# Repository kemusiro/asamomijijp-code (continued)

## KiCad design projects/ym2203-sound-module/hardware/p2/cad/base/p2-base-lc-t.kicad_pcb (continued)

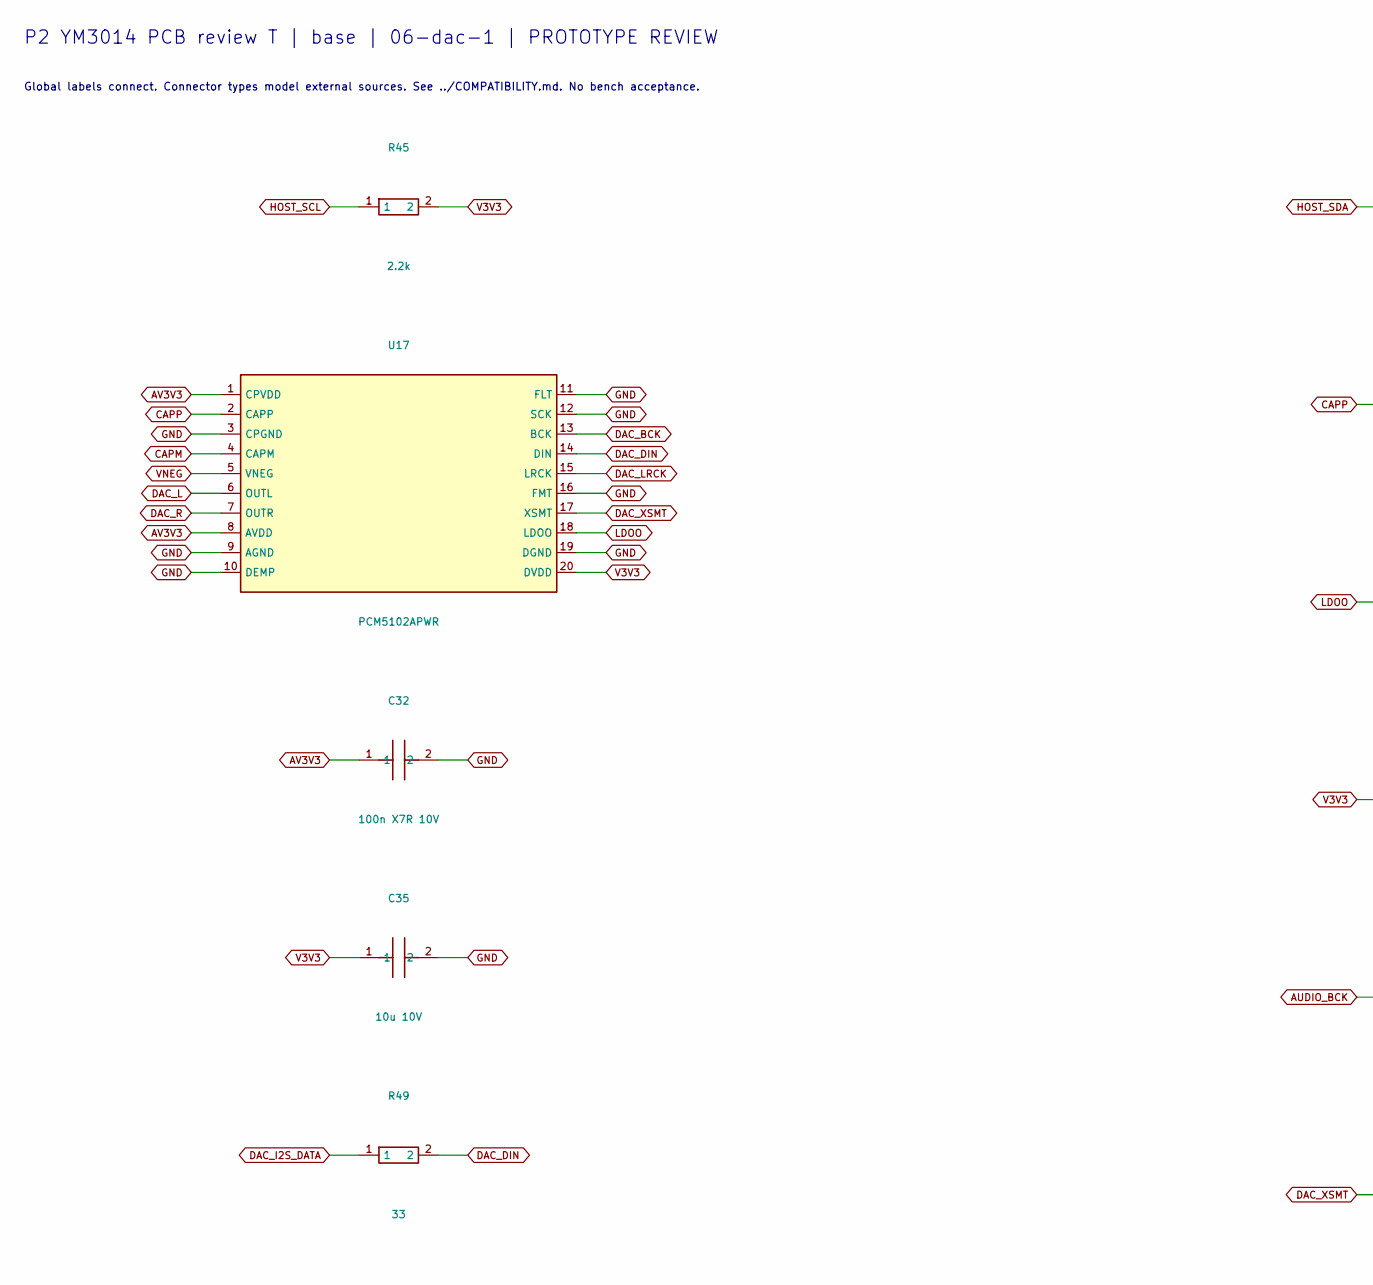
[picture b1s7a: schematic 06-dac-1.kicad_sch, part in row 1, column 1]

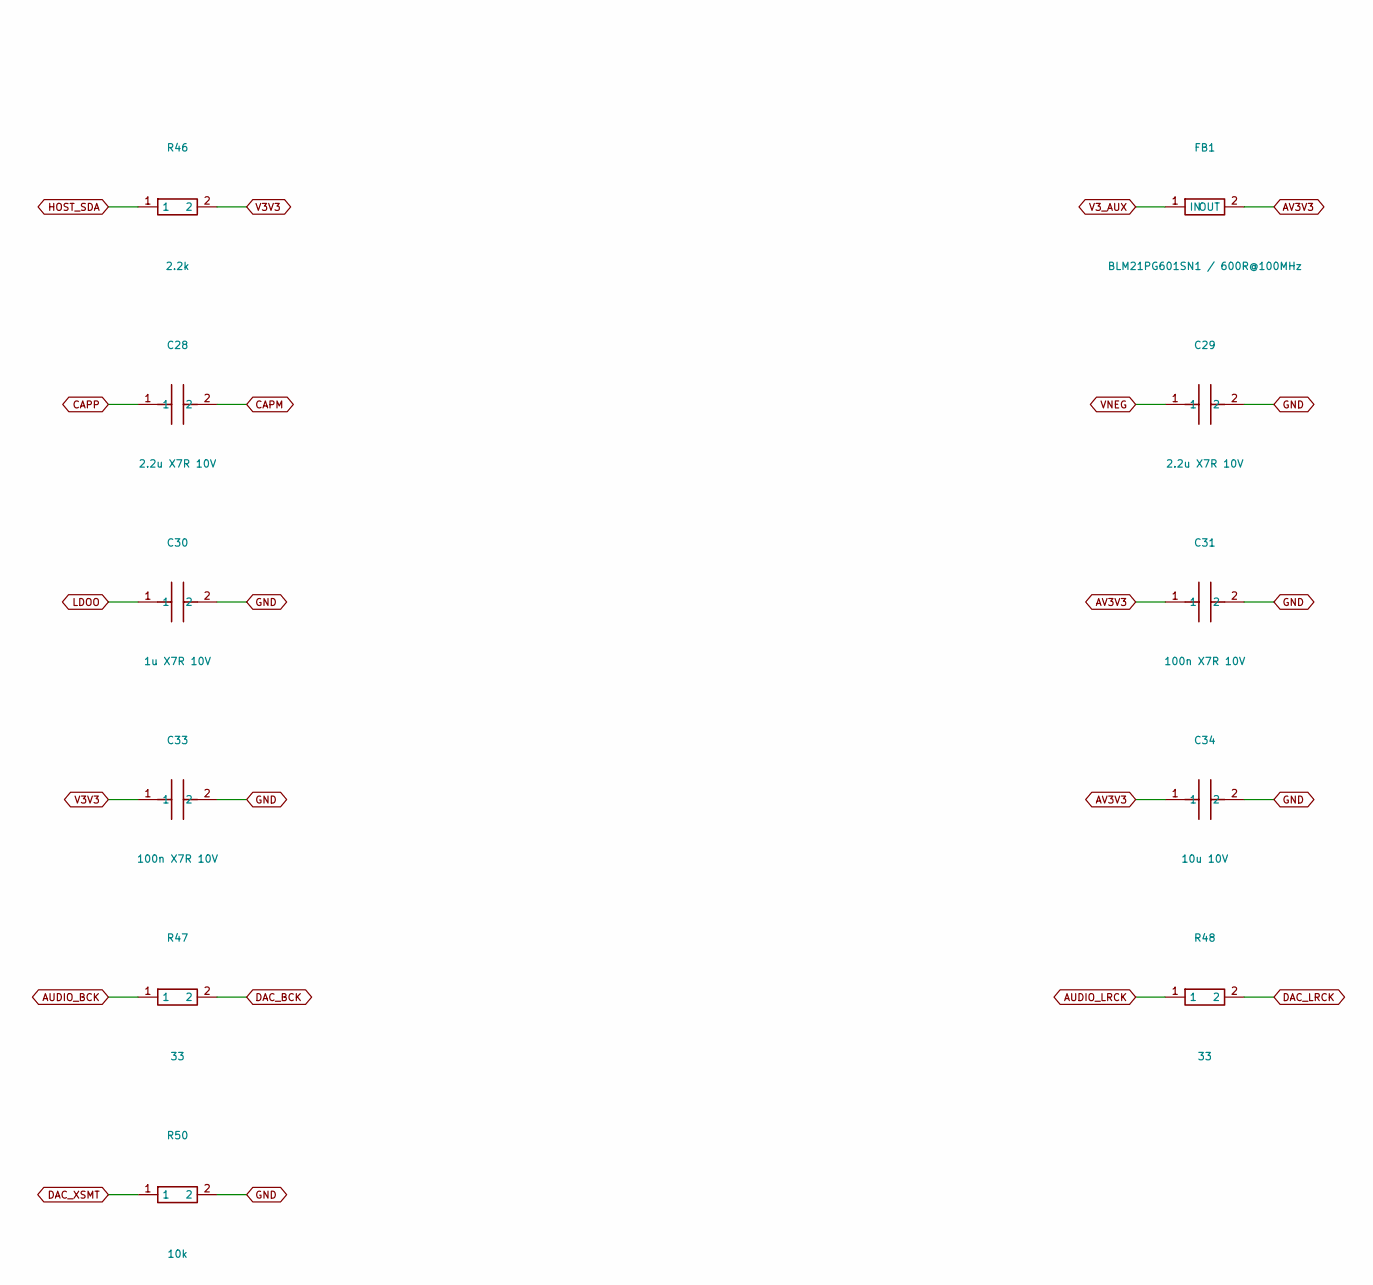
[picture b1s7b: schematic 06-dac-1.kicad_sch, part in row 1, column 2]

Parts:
C28, C29: 2.2u X7R 10V; C_0805_2012Metric
C30: 1u X7R 10V; C_0805_2012Metric
C31, C32, C33: 100n X7R 10V; C_0805_2012Metric
C34, C35: 10u 10V; C_0805_2012Metric
FB1: BLM21PG601SN1 / 600R@100MHz; L_0805_2012Metric
R45, R46: 2.2k; R_0805_2012Metric
R47, R48, R49: 33; R_0805_2012Metric
R50: 10k; R_0805_2012Metric
U17: PCM5102APWR; TSSOP-20_4.4x6.5mm_P0.65mm

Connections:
AUDIO_BCK: R47.1; also elsewhere on the board
AUDIO_LRCK: R48.1; also elsewhere on the board
AV3V3: C31.1, C32.1, C34.1, FB1.2 (OUT), U17.1 (CPVDD), U17.8 (AVDD); also elsewhere on the board
CAPM: C28.2, U17.4 (CAPM)
CAPP: C28.1, U17.2 (CAPP)
DAC_BCK: R47.2, U17.13 (BCK); also elsewhere on the board
DAC_DIN: R49.2, U17.14 (DIN); also elsewhere on the board
DAC_I2S_DATA: R49.1; also elsewhere on the board
DAC_L: U17.6 (OUTL); also elsewhere on the board
DAC_LRCK: R48.2, U17.15 (LRCK); also elsewhere on the board
DAC_R: U17.7 (OUTR); also elsewhere on the board
DAC_XSMT: R50.1, U17.17 (XSMT); also elsewhere on the board
GND: C29.2, C30.2, C31.2, C32.2, C33.2, C34.2, C35.2, R50.2, U17.3 (CPGND), U17.9 (AGND), U17.10 (DEMP), U17.11 (FLT), U17.12 (SCK), U17.16 (FMT), U17.19 (DGND); also elsewhere on the board
HOST_SCL: R45.1; also elsewhere on the board
HOST_SDA: R46.1; also elsewhere on the board
LDOO: C30.1, U17.18 (LDOO)
V3V3: C33.1, C35.1, R45.2, R46.2, U17.20 (DVDD); also elsewhere on the board
V3_AUX: FB1.1 (IN); also elsewhere on the board
VNEG: C29.1, U17.5 (VNEG)

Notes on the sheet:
P2 YM3014 PCB review T | base | 06-dac-1 | PROTOTYPE REVIEW
Global labels connect. Connector types model external sources. See ../COMPATIBILITY.md. No bench acceptance.

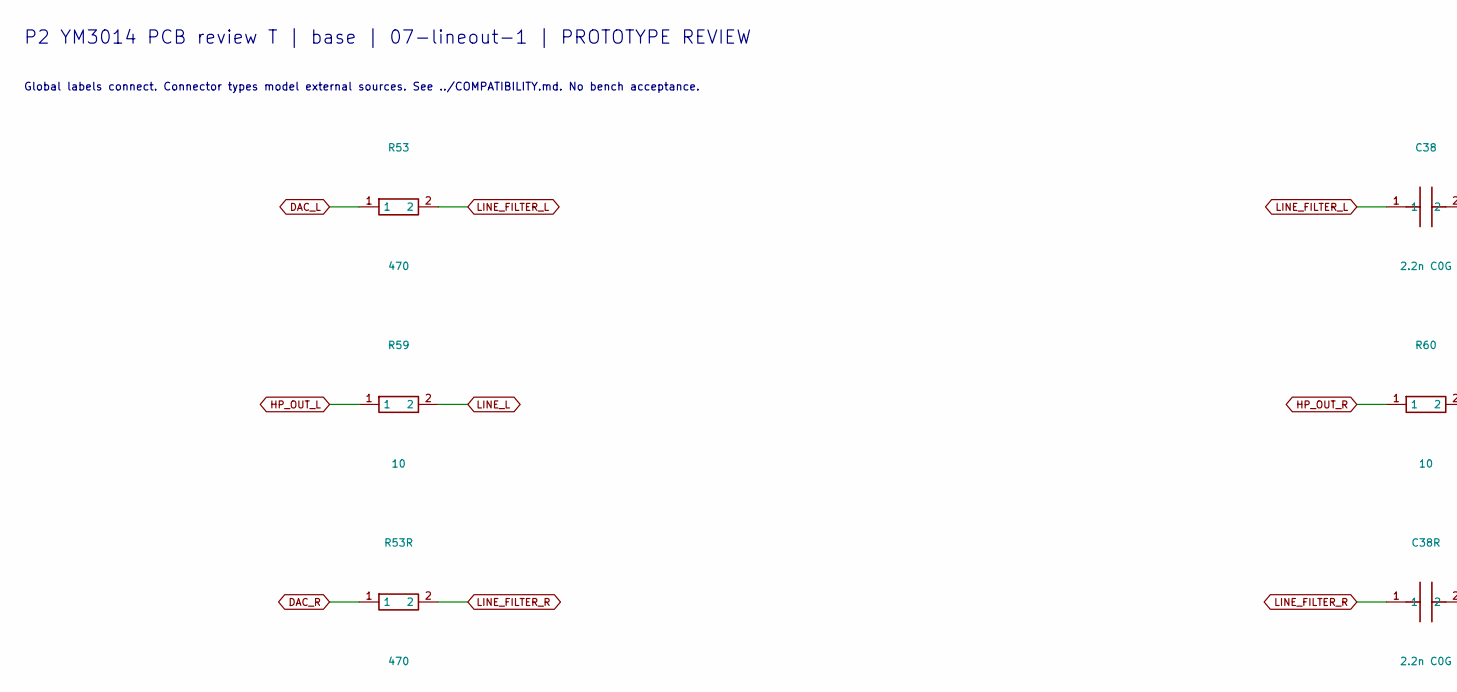
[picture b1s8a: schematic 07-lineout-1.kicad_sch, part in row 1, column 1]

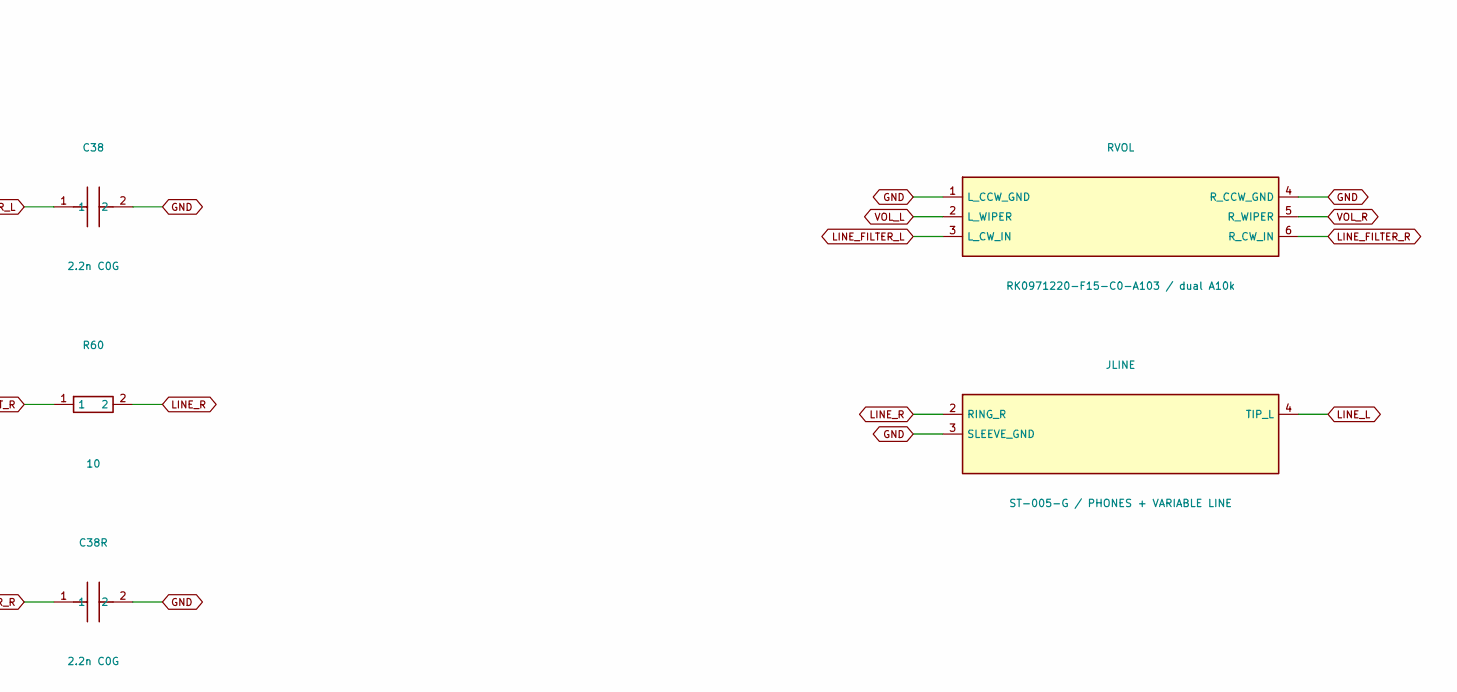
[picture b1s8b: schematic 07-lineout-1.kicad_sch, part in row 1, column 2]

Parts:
C38, C38R: 2.2n C0G; C_0805_2012Metric
JLINE: ST-005-G / PHONES + VARIABLE LINE; ST005G_TRS
R53, R53R: 470; R_0805_2012Metric
R59, R60: 10; R_0805_2012Metric
RVOL: RK0971220-F15-C0-A103 / dual A10k; RK0971220_Dual_A10k

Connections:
DAC_L: R53.1; also elsewhere on the board
DAC_R: R53R.1; also elsewhere on the board
GND: C38.2, C38R.2, JLINE.3 (SLEEVE_GND), RVOL.1 (L_CCW_GND), RVOL.4 (R_CCW_GND); also elsewhere on the board
HP_OUT_L: R59.1; also elsewhere on the board
HP_OUT_R: R60.1; also elsewhere on the board
LINE_FILTER_L: C38.1, R53.2, RVOL.3 (L_CW_IN)
LINE_FILTER_R: C38R.1, R53R.2, RVOL.6 (R_CW_IN)
LINE_L: JLINE.4 (TIP_L), R59.2; also elsewhere on the board
LINE_R: JLINE.2 (RING_R), R60.2; also elsewhere on the board
VOL_L: RVOL.2 (L_WIPER); also elsewhere on the board
VOL_R: RVOL.5 (R_WIPER); also elsewhere on the board

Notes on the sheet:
P2 YM3014 PCB review T | base | 07-lineout-1 | PROTOTYPE REVIEW
Global labels connect. Connector types model external sources. See ../COMPATIBILITY.md. No bench acceptance.

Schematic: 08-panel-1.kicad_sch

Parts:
CRGB: 100n; C_0805_2012Metric
CURGB: 100n; C_0805_2012Metric
DLED0: RX GREEN; LED_D3.0mm
DPOWER: POWER GREEN; LED_D3.0mm
DRGB: WS2812B-V6 / STATUS; LED_WS2812B_PLCC4_5.0x5.0mm_P3.2mm
DTX: TX GREEN; LED_D3.0mm
RLED0: 1k; R_0805_2012Metric
RP0, RP1, RP2, RP3, RP4, RP5: 10k; R_0805_2012Metric
RPOWER: 2.2k; R_0805_2012Metric
RRGB: 220; R_0805_2012Metric
RRGBPD: 100k; R_0805_2012Metric
RTX: 1k; R_0805_2012Metric
SWCLOCK: EDS104SZ 4-bit DIP ON=0 SW1=LSB; SW_DIP_SPSTx04_Slide_6.7x11.72mm_W7.62mm_P2.54mm_LowProfile
SWSTOP: STOP; SW_PUSH_6mm_H4.3mm
SWTEST: TEST; SW_PUSH_6mm_H4.3mm
URGB: SN74AHCT1G125DBVR; SOT-23-5

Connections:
BASE_STOP_N: RP4.2, SWSTOP.1 (A); also elsewhere on the board
DIP1_N: RP0.2, SWCLOCK.1 (SW1); also elsewhere on the board
DIP2_N: RP1.2, SWCLOCK.2 (SW2); also elsewhere on the board
DIP3_N: RP2.2, SWCLOCK.3 (SW3); also elsewhere on the board
DIP4_N: RP3.2, SWCLOCK.4 (SW4); also elsewhere on the board
GND: CRGB.2, CURGB.2, DPOWER.1 (K), DRGB.3 (GND), RRGBPD.2, SWCLOCK.5 (GND), SWCLOCK.6 (GND), SWCLOCK.7 (GND), SWCLOCK.8 (GND), SWSTOP.2 (B), SWTEST.2 (B), URGB.1 (OE_N), URGB.3 (GND); also elsewhere on the board
LED_ANODE0: DLED0.2 (A), RLED0.1
POWER_LED_A: DPOWER.2 (A), RPOWER.2
RGB_DIN: DRGB.4 (DIN), RRGB.2
RGB_DRIVER: RRGB.1, URGB.4 (Y)
RX_LED_N: DLED0.1 (K); also elsewhere on the board
STATUS_RGB_DATA: RRGBPD.1, URGB.2 (A); also elsewhere on the board
TEST_N: RP5.2, SWTEST.1 (A); also elsewhere on the board
TX_LED_A: DTX.2 (A), RTX.2
TX_LED_N: DTX.1 (K); also elsewhere on the board
V3V3: RLED0.2, RP0.1, RP1.1, RP2.1, RP3.1, RP4.1, RP5.1, RTX.1; also elsewhere on the board
V5_CARRIER: CRGB.1, CURGB.1, DRGB.1 (VDD), RPOWER.1, URGB.5 (VCC); also elsewhere on the board

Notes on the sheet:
P2 YM3014 PCB review T | base | 08-panel-1 | PROTOTYPE REVIEW
Global labels connect. Connector types model external sources. See ../COMPATIBILITY.md. No bench acceptance.

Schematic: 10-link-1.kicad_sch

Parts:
RALERT: 0; R_0805_2012Metric
RBALERT: 10k; R_0805_2012Metric
RBCS: 10k; R_0805_2012Metric
RBCTL0, RBCTL1, RBCTL2, RBCTL3: 33; R_0805_2012Metric
RBD0, RBD1, RBD2, RBD3, RBD4, RBD5, RBD6, RBD7: 33; R_0805_2012Metric
RBEN: 10k; R_0805_2012Metric
RBI1: 100k; R_0805_2012Metric
RBMISO: 100k; R_0805_2012Metric
RBMOSI: 100k; R_0805_2012Metric
RBSCK: 100k; R_0805_2012Metric
RBSD: 100k; R_0805_2012Metric
RLKBCK: 33; R_0805_2012Metric
RLKEN: 33; R_0805_2012Metric
RLKLR: 33; R_0805_2012Metric

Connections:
AUDIO_BCK: RLKBCK.1; also elsewhere on the board
AUDIO_LRCK: RLKLR.1; also elsewhere on the board
BUS_D0: RBD0.1, RBMISO.1; also elsewhere on the board
BUS_D1: RBCS.1, RBD1.1; also elsewhere on the board
BUS_D2: RBD2.1, RBSCK.1; also elsewhere on the board
BUS_D3: RBD3.1, RBMOSI.1; also elsewhere on the board
BUS_D4: RBD4.1; also elsewhere on the board
BUS_D5: RBD5.1; also elsewhere on the board
BUS_D6: RBD6.1; also elsewhere on the board
BUS_D7: RBD7.1; also elsewhere on the board
GND: RBEN.2, RBI1.2, RBMISO.2, RBMOSI.2, RBSCK.2, RBSD.2; also elsewhere on the board
L_BUS_D0: RBD0.2; also elsewhere on the board
L_BUS_D1: RBD1.2; also elsewhere on the board
L_BUS_D2: RBD2.2; also elsewhere on the board
L_BUS_D3: RBD3.2; also elsewhere on the board
L_BUS_D4: RBD4.2; also elsewhere on the board
L_BUS_D5: RBD5.2; also elsewhere on the board
L_BUS_D6: RBD6.2; also elsewhere on the board
L_BUS_D7: RBD7.2; also elsewhere on the board
L_MOD_ALERT_N: RALERT.1; also elsewhere on the board
L_MOD_CTL0: RBCTL0.2; also elsewhere on the board
L_MOD_CTL1: RBCTL1.2; also elsewhere on the board
L_MOD_CTL2: RBCTL2.2; also elsewhere on the board
L_MOD_CTL3: RBCTL3.2; also elsewhere on the board
L_MOD_ENABLE: RLKEN.2; also elsewhere on the board
L_MOD_I2S_BCK: RLKBCK.2; also elsewhere on the board
L_MOD_I2S_DATA: RBI1.1; also elsewhere on the board
L_MOD_I2S_LRCK: RLKLR.2; also elsewhere on the board
MOD_ALERT_N: RALERT.2, RBALERT.1; also elsewhere on the board
MOD_CTL0: RBCTL0.1; also elsewhere on the board
MOD_CTL1: RBCTL1.1; also elsewhere on the board
MOD_CTL2: RBCTL2.1; also elsewhere on the board
MOD_CTL3: RBCTL3.1; also elsewhere on the board
MOD_ENABLE: RBEN.1, RLKEN.1; also elsewhere on the board
MOD_I2S_DATA: RBSD.1; also elsewhere on the board
V3V3: RBALERT.2, RBCS.2; also elsewhere on the board

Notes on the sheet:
P2 YM3014 PCB review T | base | 10-link-1 | PROTOTYPE REVIEW
Global labels connect. Connector types model external sources. See ../COMPATIBILITY.md. No bench acceptance.

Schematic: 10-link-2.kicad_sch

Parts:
CURXDATA: 100n X7R 10V; C_0805_2012Metric
JMOD: G40 2x20 ordinary female / KEY6; G40_Female_Top
URXDATA: TC7SZ125F,LJ(CT; SOT-23-5

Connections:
AUDIO_L: JMOD.37 (AUDIO_L); also elsewhere on the board
AUDIO_R: JMOD.39 (AUDIO_R); also elsewhere on the board
GND: CURXDATA.2, JMOD.2 (GND), JMOD.4 (GND), JMOD.13 (GND), JMOD.14 (GND), JMOD.26 (GND), JMOD.28 (GND), JMOD.30 (GND), JMOD.32 (GND), JMOD.35 (GND), JMOD.36 (GND), JMOD.38 (GND), JMOD.40 (GND), URXDATA.1 (OE_N), URXDATA.3 (GND); also elsewhere on the board
L_BUS_D0: JMOD.9 (BUS_D0); also elsewhere on the board
L_BUS_D1: JMOD.10 (BUS_D1); also elsewhere on the board
L_BUS_D2: JMOD.11 (BUS_D2); also elsewhere on the board
L_BUS_D3: JMOD.12 (BUS_D3); also elsewhere on the board
L_BUS_D4: JMOD.15 (BUS_D4); also elsewhere on the board
L_BUS_D5: JMOD.16 (BUS_D5); also elsewhere on the board
L_BUS_D6: JMOD.17 (BUS_D6); also elsewhere on the board
L_BUS_D7: JMOD.18 (BUS_D7); also elsewhere on the board
L_MOD_ALERT_N: JMOD.8 (MOD_ALERT_N); also elsewhere on the board
L_MOD_CTL0: JMOD.19 (MOD_CTL0); also elsewhere on the board
L_MOD_CTL1: JMOD.20 (MOD_CTL1); also elsewhere on the board
L_MOD_CTL2: JMOD.21 (MOD_CTL2); also elsewhere on the board
L_MOD_CTL3: JMOD.22 (MOD_CTL3); also elsewhere on the board
L_MOD_ENABLE: JMOD.7 (MOD_ENABLE); also elsewhere on the board
L_MOD_I2S_BCK: JMOD.31 (MOD_I2S_BCK); also elsewhere on the board
L_MOD_I2S_DATA: JMOD.34 (MOD_I2S_DATA), URXDATA.2 (A); also elsewhere on the board
L_MOD_I2S_LRCK: JMOD.33 (MOD_I2S_LRCK); also elsewhere on the board
L_SOUND_CLK0: JMOD.25 (SOUND_CLK0); also elsewhere on the board
L_SOUND_CLK1: JMOD.27 (SOUND_CLK1); also elsewhere on the board
L_SOUND_CLK2: JMOD.29 (SOUND_CLK2); also elsewhere on the board
MOD_I2S_DATA: URXDATA.4 (Y); also elsewhere on the board
SERVICE_SCL: JMOD.24 (MOD_I2C_SCL); also elsewhere on the board
SERVICE_SDA: JMOD.23 (MOD_I2C_SDA); also elsewhere on the board
V3V3: CURXDATA.1, URXDATA.5 (VCC); also elsewhere on the board
V3_AUX: JMOD.5 (V3V3_MODULE_AUX); also elsewhere on the board
V5_CARRIER: JMOD.1 (V5_MODULE), JMOD.3 (V5_MODULE); also elsewhere on the board

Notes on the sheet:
P2 YM3014 PCB review T | base | 10-link-2 | PROTOTYPE REVIEW
Global labels connect. Connector types model external sources. See ../COMPATIBILITY.md. No bench acceptance.

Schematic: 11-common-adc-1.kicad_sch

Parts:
CADCAV0: 100n X7R 10V; C_0805_2012Metric
CADCAV1: 10u X7R 10V; C_0805_2012Metric
CADCDV0: 100n X7R 10V; C_0805_2012Metric
CADCDV1: 10u X7R 10V; C_0805_2012Metric
CADCIO0: 100n X7R 10V; C_0805_2012Metric
CADCIO1: 10u X7R 10V; C_0805_2012Metric
CADCLDO0: 100n X7R 10V; C_0805_2012Metric
CADCLDO1: 10u X7R 10V; C_0805_2012Metric
CADCVREF: 1u X7R 10V; C_0805_2012Metric
RADCBCK: 33; R_0805_2012Metric
RADCDATA: 33; R_0805_2012Metric
RADCDATAPD: 100k; R_0805_2012Metric
RADCLR: 33; R_0805_2012Metric
RDMINPD: 100k; R_0805_2012Metric
UADC: PCM1863DBT; TSSOP-30_4.4x7.8mm_P0.5mm

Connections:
ADC_BCK: RADCBCK.2, UADC.17 (BCK)
ADC_DMIN_PD: RDMINPD.1, UADC.21 (GPIO1_DMIN)
ADC_L: UADC.3 (VINL1); also elsewhere on the board
ADC_LDO_1V8: CADCLDO0.1, CADCLDO1.1, UADC.11 (LDO_1V8)
ADC_LRCK: RADCLR.2, UADC.16 (LRCK)
ADC_R: UADC.4 (VINR1); also elsewhere on the board
ADC_VREF: CADCVREF.1, UADC.6 (VREF)
AUDIO_BCK: RADCBCK.1; also elsewhere on the board
AUDIO_LRCK: RADCLR.1; also elsewhere on the board
AV3V3: CADCAV0.1, CADCAV1.1, UADC.8 (AVDD); also elsewhere on the board
BASE_ADC_DOUT: RADCDATA.2, RADCDATAPD.1; also elsewhere on the board
BASE_ADC_DOUT_RAW: RADCDATA.1, UADC.18 (DOUT)
GND: CADCAV0.2, CADCAV1.2, CADCDV0.2, CADCDV1.2, CADCIO0.2, CADCIO1.2, CADCLDO0.2, CADCLDO1.2, CADCVREF.2, RADCDATAPD.2, RDMINPD.2, UADC.7 (AGND), UADC.10 (XI), UADC.12 (DGND), UADC.15 (SCKI), UADC.25 (AD), UADC.26 (MD0_I2C); also elsewhere on the board
SERVICE_SCL: UADC.24 (SCL); also elsewhere on the board
SERVICE_SDA: UADC.23 (SDA); also elsewhere on the board
V3V3: CADCIO0.1, CADCIO1.1, UADC.14 (IOVDD); also elsewhere on the board
V3_AUX: CADCDV0.1, CADCDV1.1, UADC.13 (DVDD); also elsewhere on the board

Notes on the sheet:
P2 YM3014 PCB review T | base | 11-common-adc-1 | PROTOTYPE REVIEW
Global labels connect. Connector types model external sources. See ../COMPATIBILITY.md. No bench acceptance.

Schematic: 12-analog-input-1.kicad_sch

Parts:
CAAFL: 470p C0G; C_0805_2012Metric
CAAFR: 470p C0G; C_0805_2012Metric
CACL: 10u 50V NP +/-20% 50NXA10MEFC5X11; CP_Radial_D5.0mm_P2.00mm
CACR: 10u 50V NP +/-20% 50NXA10MEFC5X11; CP_Radial_D5.0mm_P2.00mm
DCLAMPL: BAT54S-QR; SOT-23
DCLAMPR: BAT54S-QR; SOT-23
RATTL: 6.8k 1%; R_0805_2012Metric
RATTR: 6.8k 1%; R_0805_2012Metric
RLIMITL: 2.2k 1%; R_0805_2012Metric
RLIMITR: 2.2k 1%; R_0805_2012Metric
RSHUNTL: 10k 1%; R_0805_2012Metric
RSHUNTR: 10k 1%; R_0805_2012Metric

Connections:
ADC_AC_L: CACL.2, RLIMITL.1
ADC_AC_R: CACR.2, RLIMITR.1
ADC_DIV_L: CACL.1, RATTL.2, RSHUNTL.1
ADC_DIV_R: CACR.1, RATTR.2, RSHUNTR.1
ADC_L: CAAFL.1, DCLAMPL.3 (K1_A2), RLIMITL.2; also elsewhere on the board
ADC_R: CAAFR.1, DCLAMPR.3 (K1_A2), RLIMITR.2; also elsewhere on the board
AUDIO_L: RATTL.1; also elsewhere on the board
AUDIO_R: RATTR.1; also elsewhere on the board
AV3V3: DCLAMPL.2 (K2), DCLAMPR.2 (K2); also elsewhere on the board
GND: CAAFL.2, CAAFR.2, DCLAMPL.1 (A1), DCLAMPR.1 (A1), RSHUNTL.2, RSHUNTR.2; also elsewhere on the board

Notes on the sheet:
P2 YM3014 PCB review T | base | 12-analog-input-1 | PROTOTYPE REVIEW
Global labels connect. Connector types model external sources. See ../COMPATIBILITY.md. No bench acceptance.

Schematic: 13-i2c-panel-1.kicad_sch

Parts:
CPANELPORT: 10u X7R 10V; C_0805_2012Metric
JEDIT: 110990037 Grove I2C 3V3 ONLY; Grove_110990037_RA

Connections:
GND: CPANELPORT.2, JEDIT.4 (GND); also elsewhere on the board
SERVICE_SCL: JEDIT.1 (SCL); also elsewhere on the board
SERVICE_SDA: JEDIT.2 (SDA); also elsewhere on the board
V3_AUX: CPANELPORT.1, JEDIT.3 (3V3); also elsewhere on the board

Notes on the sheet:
P2 YM3014 PCB review T | base | 13-i2c-panel-1 | PROTOTYPE REVIEW
Global labels connect. Connector types model external sources. See ../COMPATIBILITY.md. No bench acceptance.

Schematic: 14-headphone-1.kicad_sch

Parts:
CHPFLY: 4.7u 25V X7R / GRM31CR71E475KA88L; C_1206_3216Metric
CHPHF: 100n; C_0805_2012Metric
CHPINL: 10u 50V NP +/-20% 50NXA10MEFC5X11; CP_Radial_D5.0mm_P2.00mm
CHPINR: 10u 50V NP +/-20% 50NXA10MEFC5X11; CP_Radial_D5.0mm_P2.00mm
CHPOUTL: 1n C0G; C_0805_2012Metric
CHPOUTR: 1n C0G; C_0805_2012Metric
CHPVDD: 4.7u 25V X7R / GRM31CR71E475KA88L; C_1206_3216Metric
CHPVSS: 4.7u 25V X7R / GRM31CR71E475KA88L; C_1206_3216Metric
FBHP: 600R @100MHz / BLM21PG601SN1D; L_0805_2012Metric
RHPFBL: 10k 1%; R_0805_2012Metric
RHPFBR: 10k 1%; R_0805_2012Metric
RHPINL: 10k 1%; R_0805_2012Metric
RHPINR: 10k 1%; R_0805_2012Metric
RHPMUTE: 100k; R_0805_2012Metric
UHP: TPA6138A2PWR; TSSOP-14_4.4x5mm_P0.65mm

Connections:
DAC_XSMT: RHPMUTE.1, UHP.5 (MUTE_N); also elsewhere on the board
GND: CHPHF.2, CHPOUTL.2, CHPOUTR.2, CHPVDD.2, CHPVSS.2, RHPMUTE.2, UHP.1 (INR_P), UHP.4 (GND), UHP.10 (GND), UHP.14 (INL_P); also elsewhere on the board
HP_3V3: CHPHF.1, CHPVDD.1, FBHP.2, UHP.9 (VDD)
HP_AC_L: CHPINL.2, RHPINL.1
HP_AC_R: CHPINR.2, RHPINR.1
HP_CN: CHPFLY.2, UHP.7 (CN)
HP_CP: CHPFLY.1, UHP.8 (CP)
HP_FB_L: RHPFBL.2, RHPINL.2, UHP.13 (INL_N)
HP_FB_R: RHPFBR.2, RHPINR.2, UHP.2 (INR_N)
HP_OUT_L: RHPFBL.1, UHP.12 (OUTL); also elsewhere on the board
HP_OUT_R: RHPFBR.1, UHP.3 (OUTR); also elsewhere on the board
HP_VSS: CHPVSS.1, UHP.6 (NEGATIVE_SUPPLY)
LINE_L: CHPOUTL.1; also elsewhere on the board
LINE_R: CHPOUTR.1; also elsewhere on the board
V3_AUX: FBHP.1; also elsewhere on the board
VOL_L: CHPINL.1; also elsewhere on the board
VOL_R: CHPINR.1; also elsewhere on the board

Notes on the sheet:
P2 YM3014 PCB review T | base | 14-headphone-1 | PROTOTYPE REVIEW
Global labels connect. Connector types model external sources. See ../COMPATIBILITY.md. No bench acceptance.

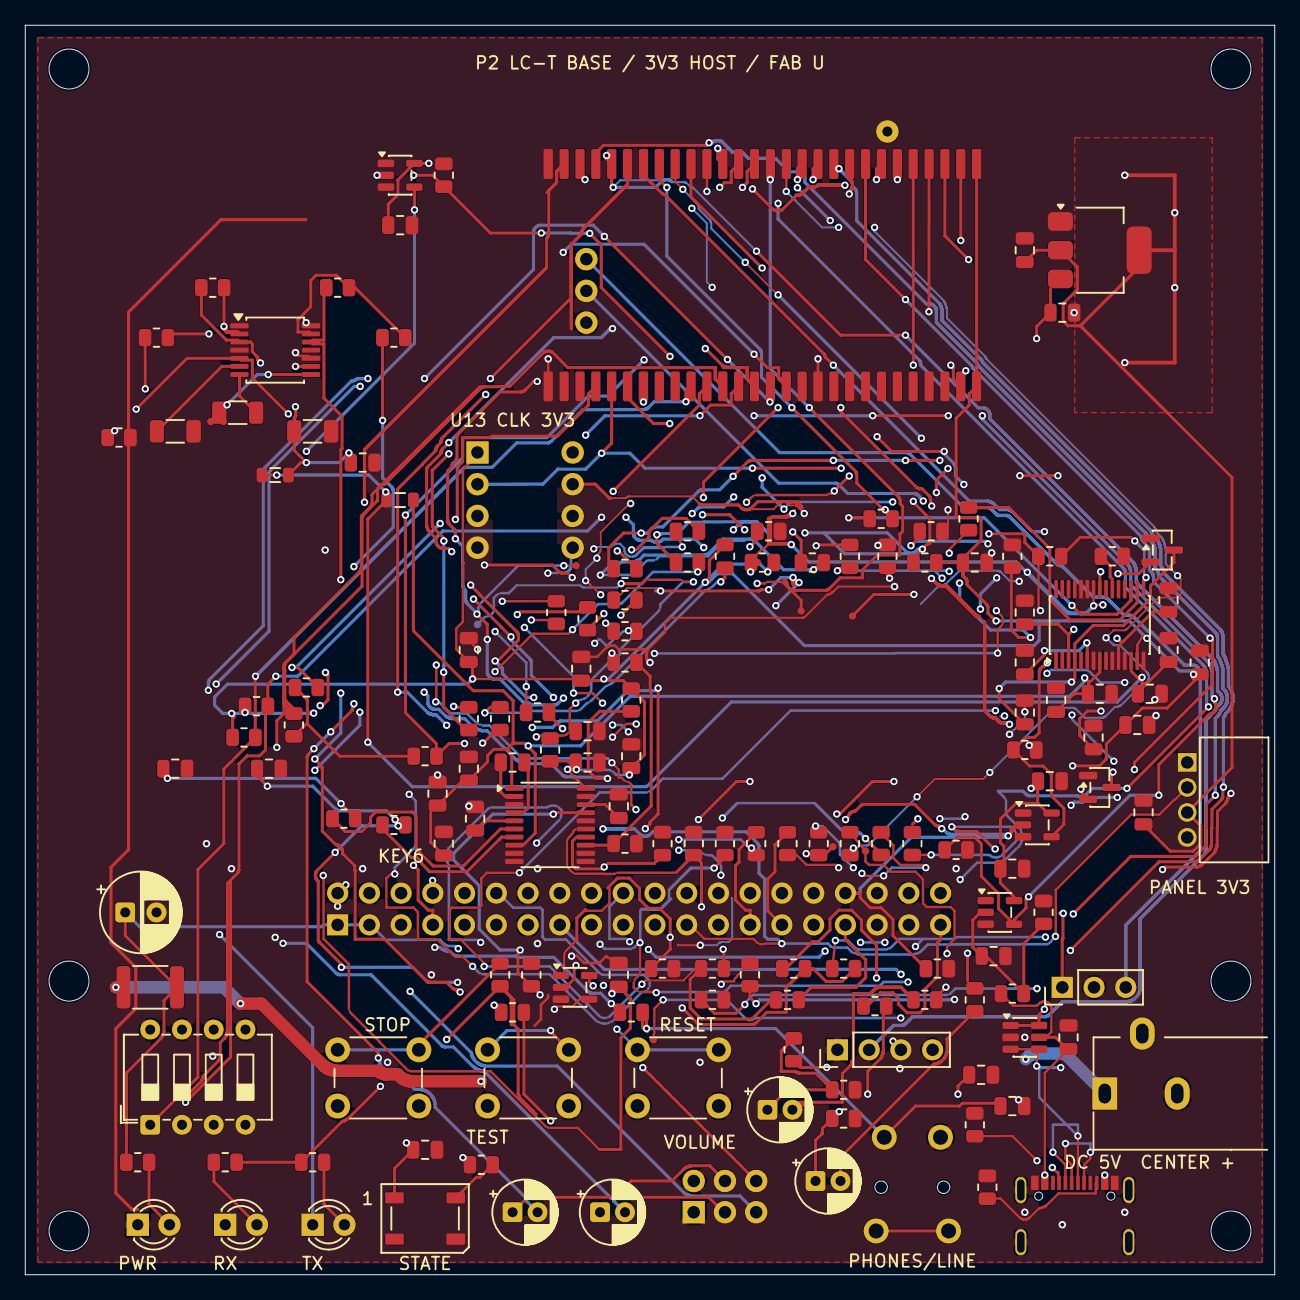
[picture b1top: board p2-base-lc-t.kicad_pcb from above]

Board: 4 copper layers, 100.0 x 100.0 mm, 161 parts (0 on the bottom side), 118 nets.

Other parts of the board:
H1, H2, H3, H4, H5, H6: M3 support

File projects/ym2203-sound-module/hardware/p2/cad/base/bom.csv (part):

Reference,Value,Footprint,Sheet,Datasheet,Note
JHOST,JHOST,Connector_PinHeader_2.54mm:PinHeader_1x04_P2.54mm_Vertical,01-module,,Existing OTHER Pico GP0 SDA / GP1 SCL; 100kHz / 0x42; NO supply pin
JSWD,JSWD,Connector_PinHeader_2.54mm:PinHeader_1x03_P2.54mm_Vertical,01-module,,3.3V SWD probe; never power carrier through probe
SWRESET,RESET,Button_Switch_THT:SW_PUSH_6mm_H4.3mm,01-module,,Two contact numbers; each has two duplicated physical pads in KiCad footprint
RRUN,10k,Resistor_SMD:R_0805_2012Metric,01-module,,
CRUN,1n C0G,Capacitor_SMD:C_0805_2012Metric,01-module,,Capacitor body/height and effective capacitance to be checked against final MPN
JPOWER,18742 / DC5V CENTER+ / Akizuki109408,P2LC:DCJack_4UCON_18742,02-power-usb,https://akizukidenshi.com/goodsaffix/18742.pdf,"5V center-positive external supply. Pin1=center +5V, pin2=outer GND, pin3=outer switched contact NC. USB VBUS remains sense/ESD only. Body14.5x9x10.7mm; mounting pattern converted from manufacturer BOTTOM view to TOP view; three plated1.0x1.6mm slots. No pin bending."
F1,MF-MSMF200/16X-2 / 2A hold@23C,Fuse:Fuse_1812_4532Metric,02-power-usb,https://bourns.com/docs/product-datasheets/mf-msmf.pdf,
C1,100u 10V,Capacitor_THT:CP_Radial_D6.3mm_P2.50mm,02-power-usb,,Capacitor body/height and effective capacitance to be checked against final MPN
C2,10u 10V,Capacitor_SMD:C_0805_2012Metric,02-power-usb,,Capacitor body/height and effective capacitance to be checked against final MPN
UESD,USBLC6-2SC6,Package_TO_SOT_SMD:SOT-23-6,02-power-usb,https://www.st.com/resource/en/datasheet/usblc6-2.pdf,"Place at USB connector, short return. VBUS protection/sense only; no external5V power path."
CVBUS,100n X7R 10V,Capacitor_SMD:C_0805_2012Metric,02-power-usb,,Capacitor body/height and effective capacitance to be checked against final MPN
RVB1,47k 1%,Resistor_SMD:R_0805_2012Metric,02-power-usb,,
RVB2,68k 1%,Resistor_SMD:R_0805_2012Metric,02-power-usb,,
CVBD,100p C0G,Capacitor_SMD:C_0805_2012Metric,02-power-usb,,Capacitor body/height and effective capacitance to be checked against final MPN
UVBUS,SN74LVC1G17DBVR,Package_TO_SOT_SMD:SOT-23-5,02-power-usb,https://www.ti.com/lit/ds/symlink/sn74lvc1g17.pdf,Ioff Schmitt;RAWVBUS47k/68k -> GP28. No USB-to-external5V supply path.
CVB3,100n X7R 10V,Capacitor_SMD:C_0805_2012Metric,02-power-usb,,Capacitor body/height and effective capacitance to be checked against final MPN
RVB3,100k,Resistor_SMD:R_0805_2012Metric,02-power-usb,,
RPDAC,10k,Resistor_SMD:R_0805_2012Metric,03-default-stop,,
RPLINE,10k,Resistor_SMD:R_0805_2012Metric,03-default-stop,,
U13,AE-Si5351A-B (110679),P2LC:AE_Si5351A_B_10x10mm,05-clock-ym,https://akizukidenshi.com/goodsaffix/AE-Si5351A.PDF,25MHz crystal included;I2C0x60;CL8pF required;module top view pins1..8;3V3 both VDD/VDDO;no GPIO change;2.54mm standoff direct solder
C21,100n X7R 10V,Capacitor_SMD:C_0805_2012Metric,05-clock-ym,,Capacitor body/height and effective capacitance to be checked against final MPN
C22,100n X7R 10V,Capacitor_SMD:C_0805_2012Metric,05-clock-ym,,Capacitor body/height and effective capacitance to be checked against final MPN
R37,4.7k 1%,Resistor_SMD:R_0805_2012Metric,05-clock-ym,,
R38,4.7k 1%,Resistor_SMD:R_0805_2012Metric,05-clock-ym,,
R45,2.2k,Resistor_SMD:R_0805_2012Metric,06-dac,,
R46,2.2k,Resistor_SMD:R_0805_2012Metric,06-dac,,
FB1,BLM21PG601SN1 / 600R@100MHz,Inductor_SMD:L_0805_2012Metric,06-dac,,
U17,PCM5102APWR,Package_SO:TSSOP-20_4.4x6.5mm_P0.65mm,06-dac,https://www.ti.com/lit/ds/symlink/pcm5102a.pdf,"Digital DVDD=BASE3V3; AVDD/CPVDD=AV3V3. Ground-centred line output, BCK PLL. XSMT is common final mute; no analog bypass."
C28,2.2u X7R 10V,Capacitor_SMD:C_0805_2012Metric,06-dac,,Capacitor body/height and effective capacitance to be checked against final MPN
C29,2.2u X7R 10V,Capacitor_SMD:C_0805_2012Metric,06-dac,,Capacitor body/height and effective capacitance to be checked against final MPN
C30,1u X7R 10V,Capacitor_SMD:C_0805_2012Metric,06-dac,,Capacitor body/height and effective capacitance to be checked against final MPN
C31,100n X7R 10V,Capacitor_SMD:C_0805_2012Metric,06-dac,,Capacitor body/height and effective capacitance to be checked against final MPN
C32,100n X7R 10V,Capacitor_SMD:C_0805_2012Metric,06-dac,,Capacitor body/height and effective capacitance to be checked against final MPN
C33,100n X7R 10V,Capacitor_SMD:C_0805_2012Metric,06-dac,,Capacitor body/height and effective capacitance to be checked against final MPN
C34,10u 10V,Capacitor_SMD:C_0805_2012Metric,06-dac,,Capacitor body/height and effective capacitance to be checked against final MPN
C35,10u 10V,Capacitor_SMD:C_0805_2012Metric,06-dac,,Capacitor body/height and effective capacitance to be checked against final MPN
R47,33,Resistor_SMD:R_0805_2012Metric,06-dac,,
R48,33,Resistor_SMD:R_0805_2012Metric,06-dac,,
R49,33,Resistor_SMD:R_0805_2012Metric,06-dac,,
R50,10k,Resistor_SMD:R_0805_2012Metric,06-dac,,
R53,470,Resistor_SMD:R_0805_2012Metric,07-lineout,,
C38,2.2n C0G,Capacitor_SMD:C_0805_2012Metric,07-lineout,,Capacitor body/height and effective capacitance to be checked against final MPN
RVOL,RK0971220-F15-C0-A103 / dual A10k,P2LC:RK0971220_Dual_A10k,07-lineout,https://akizukidenshi.com/goodsaffix/RK0971220-F15-C0-A103.pdf,"Rev C footprint and gang numbering. 1/4=CCW GND;2/5=L/R wipers;3/6=CW LINE_FILTER_L/R. Rotation viewed from shaft: clockwise increases both channels. Two inputs remain independent stereo, not tied to mono. No external harness."
R59,10,Resistor_SMD:R_0805_2012Metric,07-lineout,,Output isolation after amplifier; datasheet typical10R/1nF. Included in headphone source impedance.
R60,10,Resistor_SMD:R_0805_2012Metric,07-lineout,,Output isolation after amplifier; datasheet typical10R/1nF. Included in headphone source impedance.
JLINE,ST-005-G / PHONES + VARIABLE LINE,P2LC:ST005G_TRS,07-lineout,https://akizukidenshi.com/goodsaffix/ST-005-G.pdf,"Rev C footprint. Manufacturer2=RING R,3=SLEEVE GND,4=TIP L with two physical4 legs. No electrical pin1. 1.2mm plated signal holes,1.0mm NPTH locators. Line out, not a headphone driver. Shared grounded stereo output,16..64ohm headphones or line input. Turn volume down before insertion; high-Z line max approx1.9Vrms; headphone full-scale may clip, adjust physical knob. No fixed-level LINE output."
SWCLOCK,EDS104SZ 4-bit DIP ON=0 SW1=LSB,Button_Switch_THT:SW_DIP_SPSTx04_Slide_6.7x11.72mm_W7.62mm_P2.54mm_LowProfile,08-panel,https://akizukidenshi.com/catalog/g/g100586/,OFF/OFF/OFF/OFF=4MHz. Latched at reset only. Codes8..15 remain muted.
RP0,10k,Resistor_SMD:R_0805_2012Metric,08-panel,,
RP1,10k,Resistor_SMD:R_0805_2012Metric,08-panel,,
RP2,10k,Resistor_SMD:R_0805_2012Metric,08-panel,,
RP3,10k,Resistor_SMD:R_0805_2012Metric,08-panel,,
RP4,10k,Resistor_SMD:R_0805_2012Metric,08-panel,,
RP5,10k,Resistor_SMD:R_0805_2012Metric,08-panel,,
SWSTOP,STOP,Button_Switch_THT:SW_PUSH_6mm_H4.3mm,08-panel,,"GPIO23direct;external10k;globalmute priority,not I2C expander."
SWTEST,TEST,Button_Switch_THT:SW_PUSH_6mm_H4.3mm,08-panel,,STOP global priority; TEST only when no owner; each debounced20ms
RLED0,1k,Resistor_SMD:R_0805_2012Metric,08-panel,,
DLED0,RX GREEN,LED_THT:LED_D3.0mm,08-panel,,<=2mA sink target; RX50ms / voice shadow20ms update; not VU
RI2SD,100k,Resistor_SMD:R_0805_2012Metric,02-power-usb,,Default low while PGA IO rail is absent; DAC XSMT remains low
RI2SB,100k,Resistor_SMD:R_0805_2012Metric,02-power-usb,,Default low while PGA IO rail is absent; DAC XSMT remains low
RI2SL,100k,Resistor_SMD:R_0805_2012Metric,02-power-usb,,Default low while PGA IO rail is absent; DAC XSMT remains low
RCLK0,33,Resistor_SMD:R_0805_2012Metric,05-clock-ym,,
RCLK1,33,Resistor_SMD:R_0805_2012Metric,05-clock-ym,,
RCLK2,33,Resistor_SMD:R_0805_2012Metric,05-clock-ym,,
R53R,470,Resistor_SMD:R_0805_2012Metric,07-lineout,,
C38R,2.2n C0G,Capacitor_SMD:C_0805_2012Metric,07-lineout,,
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
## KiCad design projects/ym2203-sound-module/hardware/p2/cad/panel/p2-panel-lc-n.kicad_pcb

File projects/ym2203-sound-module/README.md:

# YM2203 sound module — 採用設計と再現用資料

非公式のYM2203実音源基板。独自ソースとCADはMIT（例外はTHIRD_PARTY_NOTICES.md）。

- **Rev C**：実機確認済み。回路・組立は[Rev C](hardware/ym2203-single-board/README.md)。
- **C版0.5.0-alpha.4**：[ファームウェア](firmware-c/README.md)、[常用手順](firmware-c/DAILY-USE-README.txt)、[HOSTプレーヤー](firmware-c/PLAYER-README.txt)。既存I2C HOST・USB-MIDI・STOP/leaseの動作を維持する。
- **P2 T/T/N・FAB U**：[採用設計](hardware/p2/README.md)。発注済み、HAL未移植、実機未受入。
- [MicroPythonからCへ移行した理由](docs/C-SDK-MIGRATION.md)。楽曲データや録音は配布しない。

元の公開履歴を書き換えず、採用設計と必要依存を抽出した。privateリポジトリ・旧レビュー・購入カートへのアクセスは不要。
固定ランタイムとC比較試験のため旧MicroPythonソースを一部残す。これをYs II向けの推奨常用版とは扱わない。
`provenance/`の取り込み記録は当時の履歴。現在の全件検査は`release-manifest.json`と以下の手順を使う。

## 検証

CPython、Cコンパイラー、KiCad10.0.5、Gerbonara1.6.3を使用する。

```sh
python3 tools/verify_export.py
python3 -m unittest discover -s firmware-c/tests -p 'test_*.py'
python3 -m unittest discover -s hardware/ym2203-single-board/firmware/tests -p 'test_*.py'
python3 hardware/ym2203-single-board/verify.py
python3 hardware/ym2203-single-board/firmware/build.py outputs/micropython-source.zip
```

C版115試験のうち4件は外部の楽曲を必要とし、`REVC_TEST_SONG`なしではskipする。他の試験は独自の短いテストデータで動く。
C SDK2.2.0/TinyUSB/picotoolは`firmware-c/toolchain-lock.json`、Arm GCCは10.3.1 20210824で固定する。

```sh
python3 firmware-c/tools/setup_sdk.py
python3 firmware-c/tools/build.py --output outputs/revc-c-demo.zip
```

SDK等は公開上流から取得して`.cache/`へ保存する。曲の指定なしでは独自の13秒診断音階・和音を使用する。
P2のERC/DRC、CAMの14異常注入、302参照の一般BOM、発注時Gerber ZIP再生成は[P2手順](hardware/p2/README.md)。

C版の既存実機受入記録は`firmware-c/verification/`。今回の抽出物の静的・ビルド検証を実機受入の追加とは扱わない。
対応記事：[Rev Cの回路とファームウェア](https://asamomiji.jp/articles/ym2203-revc-sound-module/)。サイトのビルドは本ソースやprivate環境から独立する。

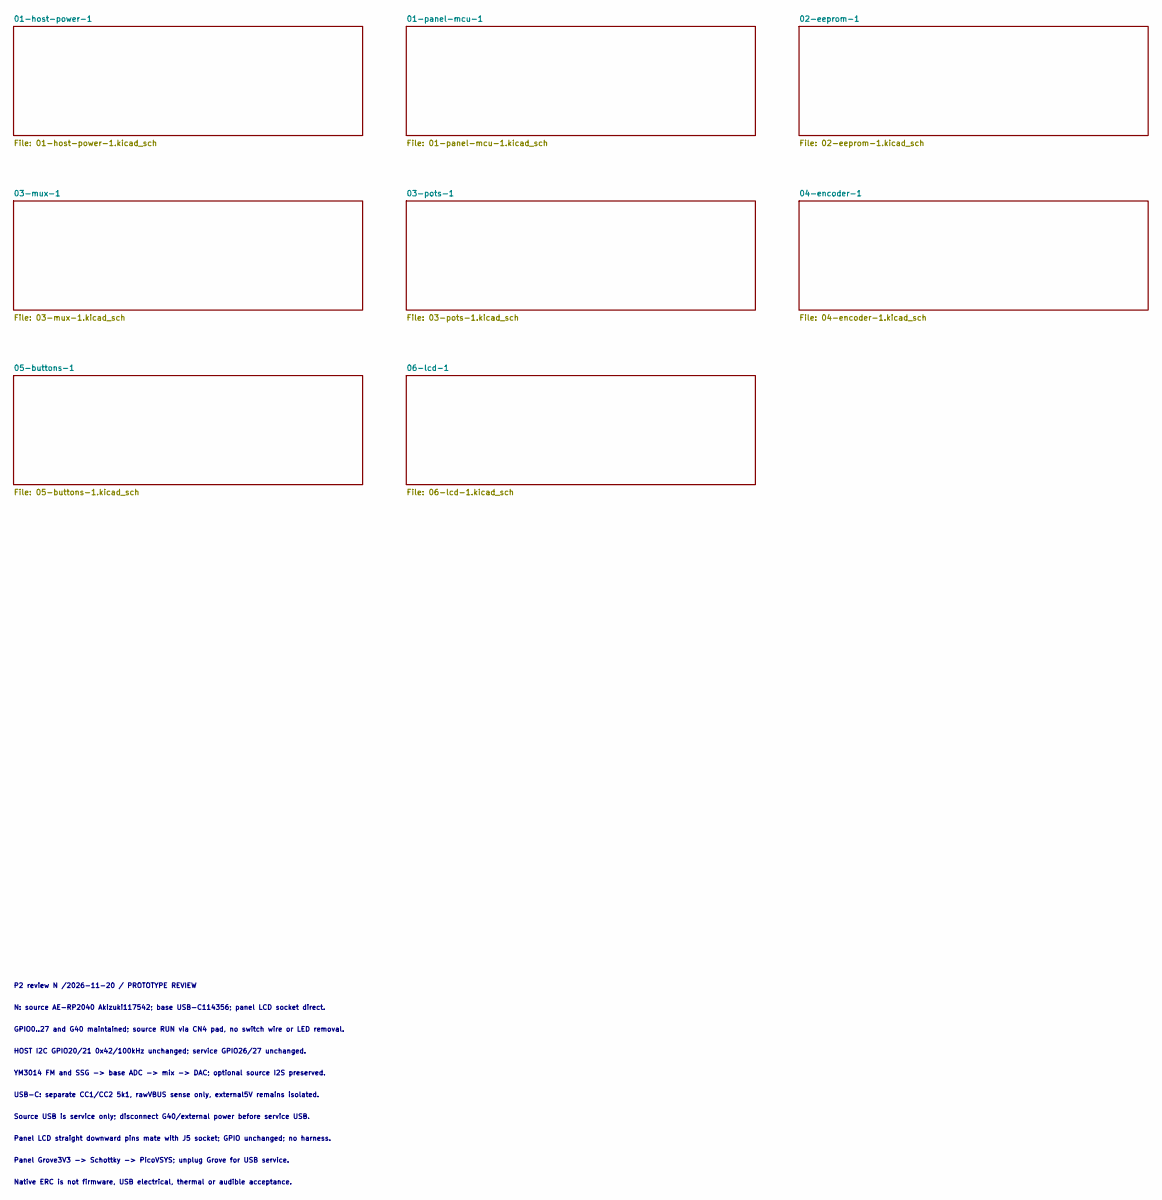
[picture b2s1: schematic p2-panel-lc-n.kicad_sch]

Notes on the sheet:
P2 review N /2026-11-20 / PROTOTYPE REVIEW
N: source AE-RP2040 Akizuki117542; base USB-C114356; panel LCD socket direct.
GPIO0..27 and G40 maintained; source RUN via CN4 pad, no switch wire or LED removal.
HOST I2C GPIO20/21 0x42/100kHz unchanged; service GPIO26/27 unchanged.
YM3014 FM and SSG -> base ADC -> mix -> DAC; optional source I2S preserved.
USB-C: separate CC1/CC2 5k1, rawVBUS sense only, external5V remains isolated.
Source USB is service only; disconnect G40/external power before service USB.
Panel LCD straight downward pins mate with J5 socket; GPIO unchanged; no harness.
Panel Grove3V3 -> Schottky -> PicoVSYS; unplug Grove for USB service.
Native ERC is not firmware, USB electrical, thermal or audible acceptance.
